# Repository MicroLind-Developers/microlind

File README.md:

# µLind
A 6809/6309 based micro computer with advanced memory and irq handling.

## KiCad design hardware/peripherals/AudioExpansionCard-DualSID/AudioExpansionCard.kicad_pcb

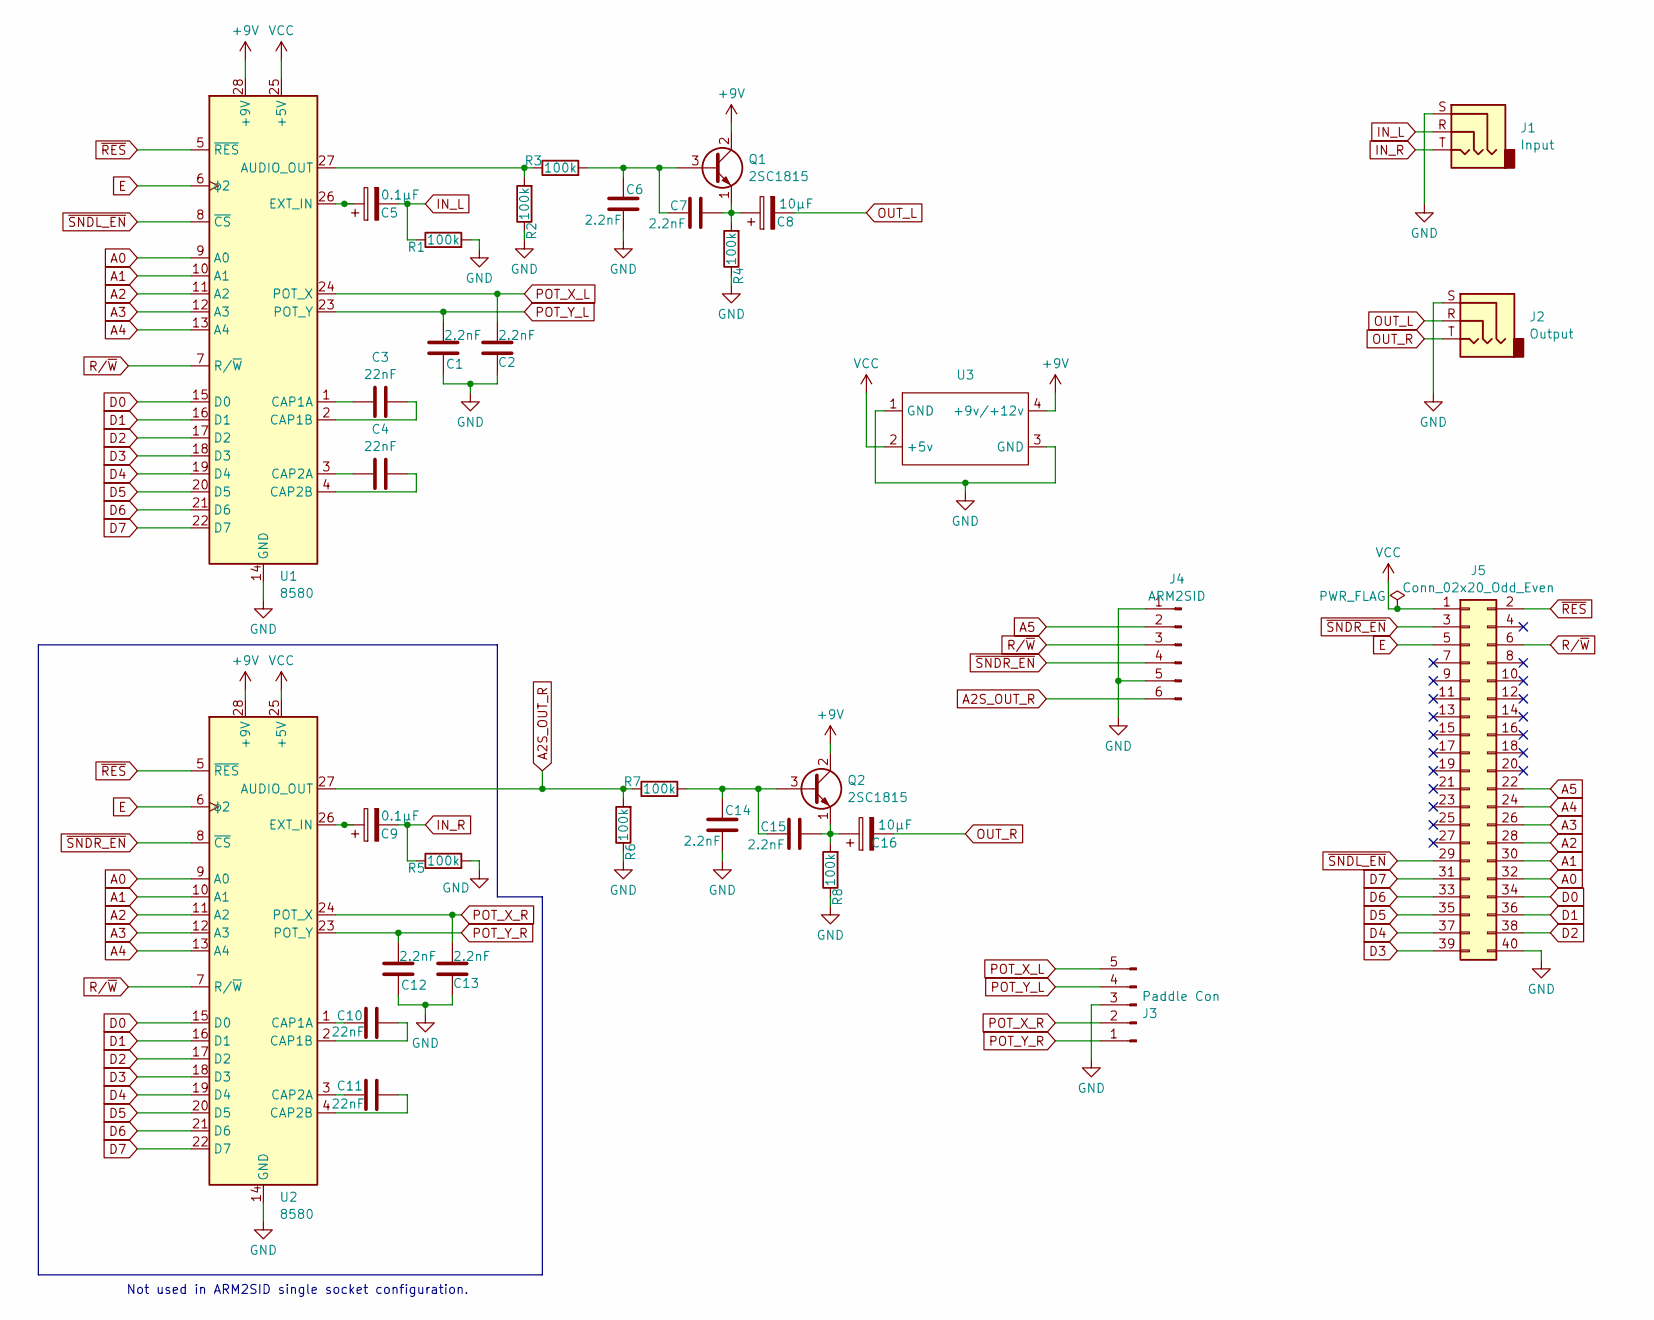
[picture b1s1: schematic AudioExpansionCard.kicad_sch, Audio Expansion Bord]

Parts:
C1, C2, C6, C7, C12, C13, C14, C15: 2.2nF; C_Disc_D3.0mm_W1.6mm_P2.50mm
C3, C4, C10, C11: 22nF; C_Disc_D3.0mm_W1.6mm_P2.50mm
C5, C9: 0.1µF; CP_Radial_D4.0mm_P1.50mm
C8, C16: 10µF; CP_Radial_D4.0mm_P1.50mm
J1: Input; Jack_3.5mm_CUI_SJ1-3533NG_Horizontal
J2: Output; Jack_3.5mm_CUI_SJ1-3533NG_Horizontal
J3: Paddle Con; PinHeader_1x05_P2.54mm_Horizontal
J4: ARM2SID; Molex_PicoBlade_53047-0610_1x06_P1.25mm_Vertical
J5: Conn_02x20_Odd_Even; AudioExpansionCard
Q1, Q2: 2SC1815; TO-92_Inline
R1, R2, R3, R4, R5, R6, R7, R8: 100k; R_Axial_DIN0207_L6.3mm_D2.5mm_P10.16mm_Horizontal
U1, U2: 8580; DIP-28_W15.24mm
U3: StepUpConverter

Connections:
+9V: Q1.2 (C), Q2.2 (C), U1.28 (+9V), U2.28 (+9V), U3.4 (+9v/+12v)
A0: J5.32, U1.9 (A0), U2.9 (A0)
A1: J5.30, U1.10 (A1), U2.10 (A1)
A2: J5.28, U1.11 (A2), U2.11 (A2)
A2S_OUT_R: J4.6, R6.2, R7.1, U2.27 (AUDIO_OUT)
A3: J5.26, U1.12 (A3), U2.12 (A3)
A4: J5.24, U1.13 (A4), U2.13 (A4)
A5: J4.2, J5.22
D0: J5.34, U1.15 (D0), U2.15 (D0)
D1: J5.36, U1.16 (D1), U2.16 (D1)
D2: J5.38, U1.17 (D2), U2.17 (D2)
D3: J5.39, U1.18 (D3), U2.18 (D3)
D4: J5.37, U1.19 (D4), U2.19 (D4)
D5: J5.35, U1.20 (D5), U2.20 (D5)
D6: J5.33, U1.21 (D6), U2.21 (D6)
D7: J5.31, U1.22 (D7), U2.22 (D7)
E: J5.5, U1.6 (ϕ2), U2.6 (ϕ2)
GND: C1.2, C2.2, C6.2, C12.2, C13.2, C14.2, J1.S, J2.S, J3.3, J4.1, J4.5, J5.40, R1.2, R2.1, R4.1, R5.2, R6.1, R8.1, U1.14 (GND), U2.14 (GND), U3.1 (GND), U3.3 (GND)
IN_L: C5.2, J1.R, R1.1
IN_R: C9.2, J1.T, R5.1
unnamed: C6.1, C7.1, Q1.3 (B), R3.2
unnamed: C7.2, C8.1, Q1.1 (E), R4.2
unnamed: C14.1, C15.1, Q2.3 (B), R7.2
unnamed: C15.2, C16.1, Q2.1 (E), R8.2
unnamed: R2.2, R3.1, U1.27 (AUDIO_OUT)
unnamed: C3.1, U1.1 (CAP1A)
unnamed: C3.2, U1.2 (CAP1B)
unnamed: C4.1, U1.3 (CAP2A)
unnamed: C4.2, U1.4 (CAP2B)
unnamed: C5.1, U1.26 (EXT_IN)
unnamed: C10.1, U2.1 (CAP1A)
unnamed: C10.2, U2.2 (CAP1B)
unnamed: C11.1, U2.3 (CAP2A)
unnamed: C11.2, U2.4 (CAP2B)
unnamed: C9.1, U2.26 (EXT_IN)
OUT_L: C8.2, J2.R
OUT_R: C16.2, J2.T
POT_X_L: C2.1, J3.5, U1.24 (POT_X)
POT_X_R: C13.1, J3.2, U2.24 (POT_X)
POT_Y_L: C1.1, J3.4, U1.23 (POT_Y)
POT_Y_R: C12.1, J3.1, U2.23 (POT_Y)
R/~W: J4.3, J5.6, U1.7 (R/~W), U2.7 (R/~W)
VCC: J5.1, U1.25 (+5V), U2.25 (+5V), U3.2 (+5v)
~RES: J5.2, U1.5 (~RES), U2.5 (~RES)
~SNDL_EN: J5.29, U1.8 (~CS)
~SNDR_EN: J4.4, J5.3, U2.8 (~CS)

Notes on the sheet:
Not used in ARM2SID single socket configuration.

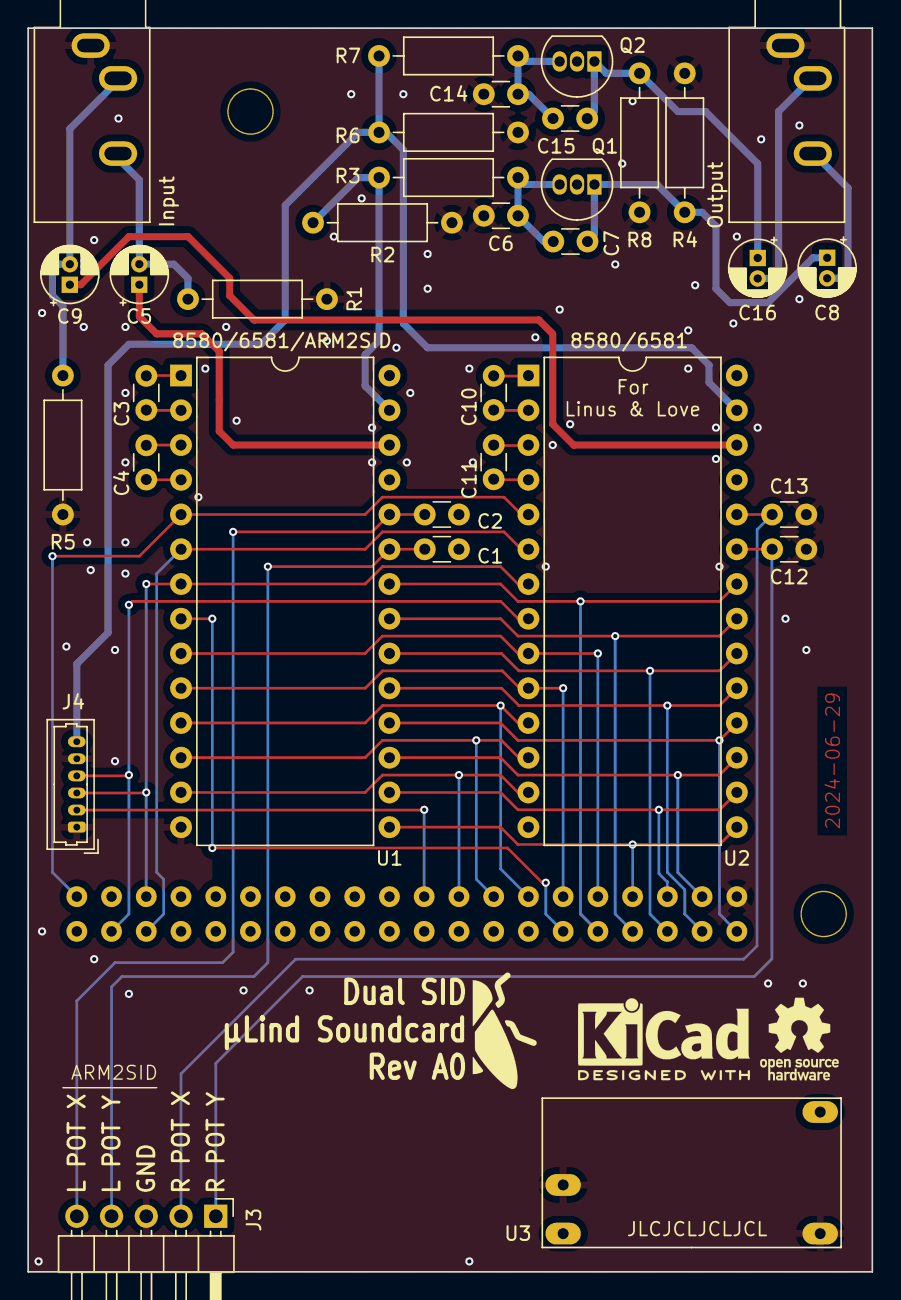
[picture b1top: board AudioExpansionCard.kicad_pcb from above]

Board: 4 copper layers, 61.7 x 90.9 mm, 34 parts (0 on the bottom side), 46 nets.

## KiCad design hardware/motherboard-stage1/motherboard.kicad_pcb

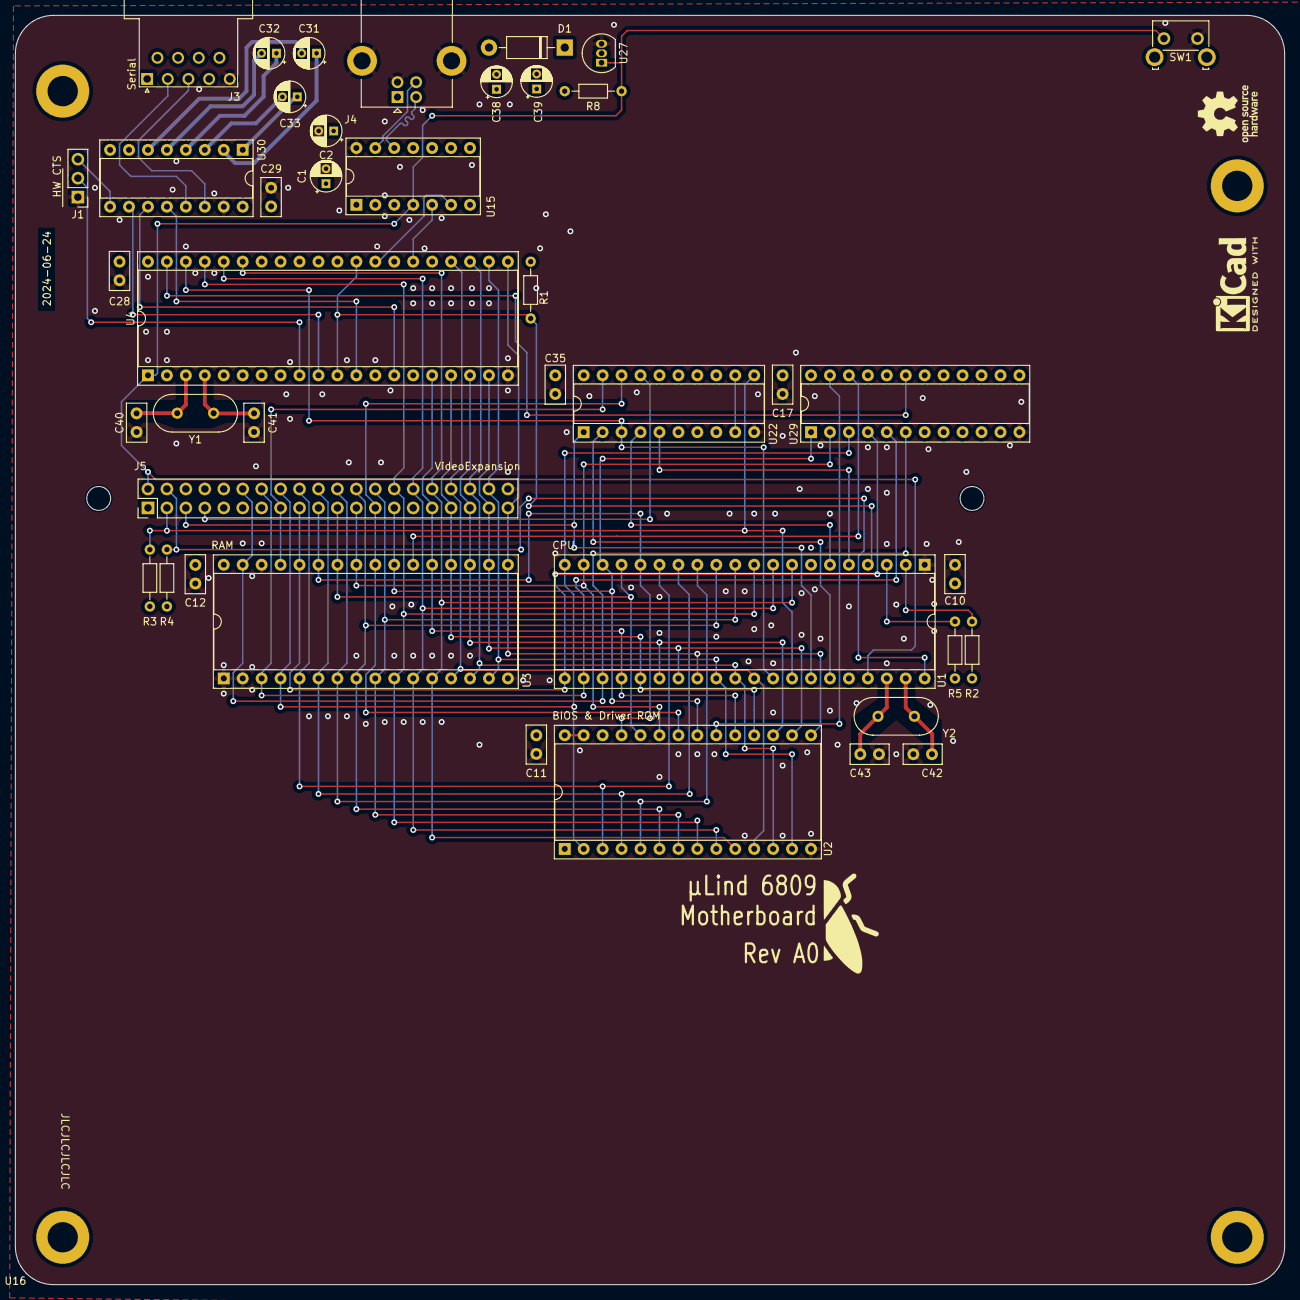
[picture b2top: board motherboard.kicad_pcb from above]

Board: 4 copper layers, 170.2 x 170.2 mm, 44 parts (0 on the bottom side), 69 nets.

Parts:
C1, C2, C31, C32, C33: 1u; CP_Radial_D4.0mm_P2.00mm
C10, C11, C12, C17, C28, C29, C35: C; C_Disc_D5.0mm_W2.5mm_P2.50mm
C38: 100µF; CP_Radial_D4.0mm_P2.00mm
C39: 10µF; CP_Radial_D4.0mm_P2.00mm
C40, C41: 43pF; C_Disc_D5.0mm_W2.5mm_P2.50mm
C42, C43: 24pF; C_Disc_D5.0mm_W2.5mm_P2.50mm
D1: 1N4007; D_DO-41_SOD81_P10.16mm_Horizontal
H6, H8: MountingHole; MountingHole_3.2mm_M3_ISO7380
J1: HW CTS; PinHeader_1x03_P2.54mm_Vertical
J3: Serial; DSUB-9_Female_Horizontal_P2.77x2.84mm_EdgePinOffset9.40mm
J4: Console; USB_B_Lumberg_2411_02_Horizontal
J5: VideoExpansion; PinHeader_2x20_P2.54mm_Vertical
R1, R2, R3, R4, R5, R8: 4k7; R_Axial_DIN0204_L3.6mm_D1.6mm_P7.62mm_Horizontal
SW1: Reset; SW_SPST_Omron_B3F-315x_Angled
U1: MC6809; DIP-40_W15.24mm_Socket
U2: 28C64; DIP-28_W15.24mm_Socket
U3: AS6C4008; DIP-32_W15.24mm_Socket
U4: DIP-40_W15.24mm_Socket
U15: MCP2221A; DIP-14_W7.62mm_Socket
U16: mITX
U22: GAL16V8; DIP-20_W7.62mm_Socket
U27: DS1813; TO-92_Inline
U29: GAL 22V10; DIP-24_W7.62mm_Socket
U30: MAX232; DIP-16_W7.62mm_Socket
Y1, Y2: Crystal; Crystal_HC49-U_Vertical

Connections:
/A0: J5.32, U1.8 (A0), U2.10 (A0), U3.12 (A0), U4.35 (RS0)
/A1: J5.30, U1.9 (A1), U2.9 (A1), U3.11 (A1), U4.36 (RS1)
/A2: J5.28, U1.10 (A2), U2.8 (A2), U3.10 (A2), U4.37 (RS2)
/A3: J5.26, U1.11 (A3), U2.7 (A3), U3.9 (A3)
/A4: J5.24, U1.12 (A4), U2.6 (A4), U3.8 (A4)
/A5: J5.22, U1.13 (A5), U2.5 (A5), U3.7 (A5)
/A6: J5.20, U1.14 (A6), U2.4 (A6), U3.6 (A6)
/A7: J5.18, U1.15 (A7), U2.3 (A7), U3.5 (A7)
/A8: J5.19, U1.16 (A8), U2.25 (A8), U3.27 (A8)
/A9: J5.21, U1.17 (A9), U2.24 (A9), U3.26 (A9)
/A10: J5.27, U1.18 (A10), U2.21 (A10), U3.23 (A10), U29.1 (I1/CLK)
/A11: J5.23, U1.19 (A11), U2.23 (A11), U3.25 (A11), U29.2 (I2)
/A12: J5.16, U1.20 (A12), U2.2 (A12), U3.4 (A12), U29.3 (I3)
/A13: J5.17, U1.21 (A13), U3.28 (A13), U29.4 (I4)
/A14: J5.14, U1.22 (A14), U3.3 (A14), U29.5 (I5)
/A15: J5.12, U1.23 (A15), U3.31 (A15), U29.6 (I6)
/Address-Logic/BA: U1.6 (BA), U22.4 (I4)
/Address-Logic/BS: U1.5 (BS), U22.5 (I5)
/Address-Logic/Q: U1.35 (Q), U22.2 (I2)
/Address-Logic/R/~W: U1.32 (R/~W), U4.38 (R~W), U22.3 (I3)
/Address-Logic/~RAM_EN: U3.22 (CE#), U29.22 (IO2)
/Address-Logic/~ROM_EN: U2.20 (~CE), U29.23 (IO1)
/Address-Logic/~SER_EN: U4.39 (~CS), U29.19 (IO5)
/CPU_MEM/~FIRQ: R1.1, U1.4 (~FIRQ), U4.11 (~IRQ2), U4.29 (~IRQ1)
/CPU_MEM/~HALT: J5.4, R4.1, U1.40 (~HALT)
/CPU_MEM/~IRQ: R5.1, U1.3 (~IRQ)
/CPU_MEM/~NMI: R2.1, U1.2 (~NMI)
/D0: J5.34, U1.31 (D0), U2.11 (D0), U3.13 (DQ0), U4.24 (D0)
/D1: J5.36, U1.30 (D1), U2.12 (D1), U3.14 (DQ1), U4.23 (D1)
/D2: J5.38, U1.29 (D2), U2.13 (D2), U3.15 (DQ2), U4.22 (D2)
/D3: J5.39, U1.28 (D3), U2.15 (D3), U3.17 (DQ3), U4.21 (D3)
/D4: J5.37, U1.27 (D4), U2.16 (D4), U3.18 (DQ4), U4.19 (D4)
/D5: J5.35, U1.26 (D5), U2.17 (D5), U3.19 (DQ5), U4.18 (D5)
/D6: J5.33, U1.25 (D6), U2.18 (D6), U3.20 (DQ6), U4.17 (D6)
/D7: J5.31, U1.24 (D7), U2.19 (D7), U3.21 (DQ7), U4.16 (D7)
/Expansion Ports/BAVAIL: J5.7, U22.17 (I03)
/Expansion Ports/E: J5.5, U1.34 (E), U22.1 (I1/CLK)
/Expansion Ports/~BREQ: J5.3, R3.1, U1.33 (~DMA/BREQ), U22.11 (I10/~OE)
/Expansion Ports/~RD: J5.25, U2.22 (~OE), U3.24 (OE#), U22.18 (IO2)
/Expansion Ports/~RST: J5.2, R8.2, SW1.1, U1.37 (~RESET), U4.1 (~RST), U15.4 (~RST), U27.1 (~RST)
/Expansion Ports/~WR: J5.15, U3.29 (WE#), U22.19 (IO1)
/Serial-Parallel/D+: J4.3 (D+), U15.13 (D+)
/Serial-Parallel/D-: J4.2 (D-), U15.12 (D-)
GND: C1.2, C2.2, C10.2, C11.2, C12.2, C17.2, C28.2, C29.2, C35.2, C40.2, C41.2, C42.2, C43.2, J1.1, J3.5, J4.4 (GND), J4.5 (Shield), J5.40, SW1.2, U1.1 (VSS), U2.14 (GND), U3.1 (A18), U3.2 (A16), U3.16 (VSS), U3.30 (A17), U4.20 (Vss), U15.14 (VSS), U22.10 (GND), U27.3 (GND), U29.12 (GND), U30.15 (GND)
unnamed: J1.2, U4.9 (~CTS2)
unnamed: J1.3, U30.9 (R2OUT)
unnamed: C43.1, U1.38 (EXTAL), Y2.1
unnamed: C42.1, U1.39 (XTAL), Y2.2
unnamed: C40.1, U4.3 (X1), Y1.2
unnamed: C41.1, U4.4 (X2), Y1.1
unnamed: U4.26 (TxD1), U15.5 (URx)
unnamed: U4.28 (RxD1), U15.6 (UTx)
unnamed: C2.1, U15.11 (VUSB)
unnamed: C33.1, U30.1 (C1+)
unnamed: C33.2, U30.3 (C1-)
unnamed: C32.1, U30.4 (C2+)
unnamed: C32.2, U30.5 (C2-)
unnamed: J3.2, U30.13 (R1IN)
unnamed: U4.12 (RxD2), U30.12 (R1OUT)
unnamed: J3.8, U30.8 (R2IN)
unnamed: U4.14 (TxD2), U30.11 (T1IN)
unnamed: J3.3, U30.14 (T1OUT)
unnamed: U4.10 (~RTS2), U30.10 (T2IN)
unnamed: J3.7, U30.7 (T2OUT)
unnamed: C31.1, U30.2 (VS+)
unnamed: C31.2, U30.6 (VS-)
VBUS: C1.1, C38.1, C39.1, D1.2 (A), J4.1 (VBUS), U15.1 (VDD)
VCC: C10.1, C11.1, C12.1, C17.1, C28.1, C29.1, C35.1, C38.2, C39.2, D1.1 (K), J5.1, R1.2, R2.2, R3.2, R4.2, R5.2, R8.1, U1.7 (VCC), U2.27 (~WE), U2.28 (VCC), U3.32 (VCC), U4.40 (VCC), U22.20 (VCC), U27.2 (VCC), U29.24 (VCC), U30.16 (VCC)
~RD': U22.9 (I9), U22.12 (IO8)

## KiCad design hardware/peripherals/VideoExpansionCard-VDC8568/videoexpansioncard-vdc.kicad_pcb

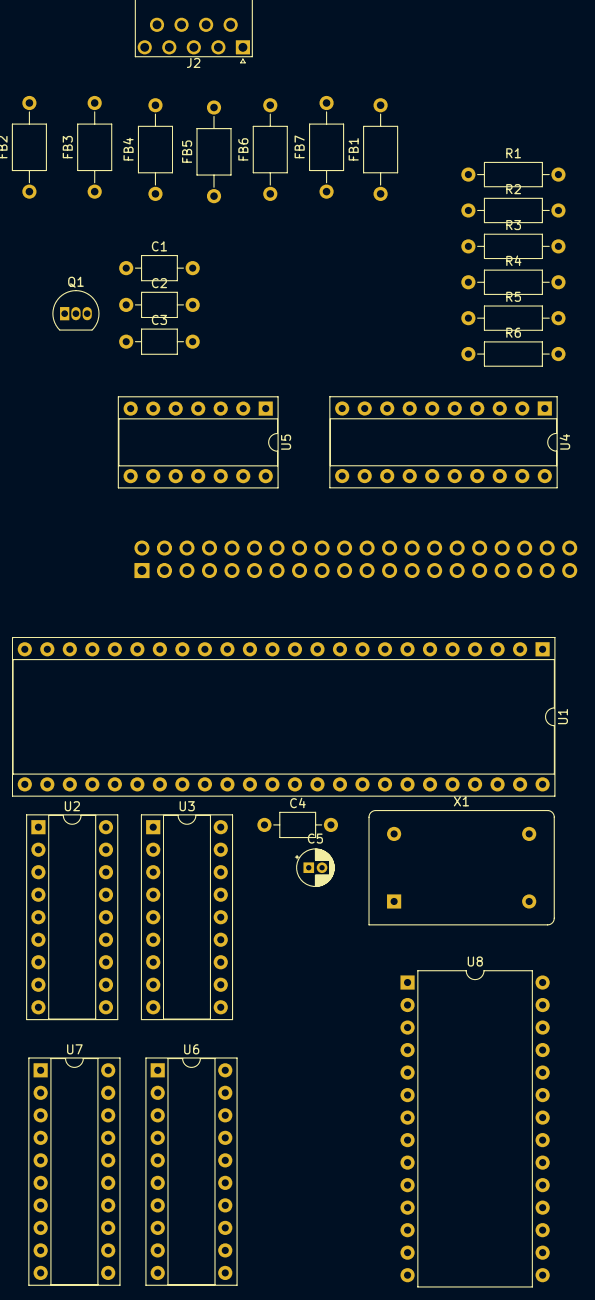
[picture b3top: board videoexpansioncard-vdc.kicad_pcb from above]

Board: 2 copper layers, 30 parts (1 on the bottom side), 69 nets, no tracks yet.

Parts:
C1, C4: 100nF; C_Axial_L3.8mm_D2.6mm_P7.50mm_Horizontal
C2, C3: 220nF; C_Axial_L3.8mm_D2.6mm_P7.50mm_Horizontal
C5: 10µF; CP_Radial_D4.0mm_P1.50mm
FB1, FB2, FB3, FB4, FB5, FB6, FB7: FerriteBead_Small; L_Axial_L5.0mm_D3.6mm_P10.00mm_Horizontal_Murata_BL01RN1A2A2
J1: VEP; PinSocket_2x20_P2.54mm_Vertical
J2: DE9_Plug; DSUB-9_Male_Horizontal_P2.77x2.54mm_EdgePinOffset9.40mm
Q1: 2SC1815; TO-92_Inline
R1, R2: 120; R_Axial_DIN0207_L6.3mm_D2.5mm_P10.16mm_Horizontal
R3: 100; R_Axial_DIN0207_L6.3mm_D2.5mm_P10.16mm_Horizontal
R4: 330; R_Axial_DIN0207_L6.3mm_D2.5mm_P10.16mm_Horizontal
R5: 47; R_Axial_DIN0207_L6.3mm_D2.5mm_P10.16mm_Horizontal
R6: 82; R_Axial_DIN0207_L6.3mm_D2.5mm_P10.16mm_Horizontal
U1: 8568; DIP-48_W15.24mm_Socket
U2, U3: DIP-18_W7.62mm_Socket
U4: 74HCT244; DIP-20_W7.62mm_Socket
U5: 74LS07; DIP-14_W7.62mm_Socket
U6: 74HCT273; DIP-20_W7.62mm_Socket
U7: GAL16V8; DIP-20_W7.62mm_Socket
U8: 27C64; DIP-28_W15.24mm
X1: ACO-16MHz; Oscillator_DIP-14

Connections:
/DRAM.DA0: U1.26 (DA0), U2.14 (A0), U3.14 (A0)
/DRAM.DA1: U1.27 (DA1), U2.13 (A1), U3.13 (A1)
/DRAM.DA2: U1.28 (DA2), U2.12 (A2), U3.12 (A2)
/DRAM.DA3: U1.29 (DA3), U2.11 (A3), U3.11 (A3)
/DRAM.DA4: U1.30 (DA4), U2.8 (A4), U3.8 (A4)
/DRAM.DA5: U1.31 (DA5), U2.7 (A5), U3.7 (A5)
/DRAM.DA6: U1.32 (DA6), U2.6 (A6), U3.6 (A6)
/DRAM.DA7: U1.33 (DA7), U2.10 (A7), U3.10 (A7)
/DRAM.DD0: U1.34 (DD0), U2.2 (D0)
/DRAM.DD1: U1.35 (DD1), U2.3 (D1)
/DRAM.DD2: U1.36 (DD2), U2.15 (D2)
/DRAM.DD3: U1.38 (DD3), U2.17 (D3)
/DRAM.DD4: U1.39 (DD4), U3.2 (D0)
/DRAM.DD5: U1.40 (DD5), U3.3 (D1)
/DRAM.DD6: U1.41 (DD6), U3.15 (D2)
/DRAM.DD7: U1.42 (DD7), U3.17 (D3)
/DRAM.~CAS: U1.1 (~CAS), U2.16 (~CAS), U3.16 (~CAS)
/DRAM.~RAS: U1.48 (~RAS), U2.5 (~RAS), U3.5 (~RAS)
/DRAM.~W: U1.21 (DR/W), U2.4 (~W), U3.4 (~W)
A0: J1.32, U1.7 (~RS)
D0: J1.34, U1.18 (D0), U8.11 (D0)
D1: J1.36, U1.17 (D1), U8.12 (D1)
D2: J1.38, U1.16 (D2), U8.13 (D2)
D3: J1.39, U1.15 (D3)
D4: J1.37, U1.14 (D4)
D5: J1.35, U1.13 (D5)
D6: J1.33, U1.11 (D6)
D7: J1.31, U1.10 (D7)
GND: C1.2, C2.2, C3.2, C4.2, C5.2, J1.40, J2.1, J2.2, R1.2, R6.2, U1.12 (GND), U1.23 (INIT), U1.24 (TEST), U2.1 (~G), U2.18 (GND), U3.1 (~G), U3.18 (GND), U4.1 (1OE), U4.10 (GND), U4.11 (2A3), U4.13 (2A2), U4.19 (2OE), U5.7 (GND), U5.9, U5.11, U5.13, X1.7 (GND)
unnamed: FB1.2, J2.5
unnamed: FB2.2, J2.9
unnamed: FB3.2, J2.4
unnamed: FB4.2, J2.8
unnamed: FB5.2, J2.3
unnamed: FB6.2, J2.7
unnamed: FB7.2, J2.6
unnamed: Q1.3 (B), R3.2, R4.1, U5.4
unnamed: Q1.2 (C), R5.2
unnamed: FB6.1, Q1.1 (E), R6.1
unnamed: R1.1, R2.1, U5.6
unnamed: R2.2, R3.1, U5.2
unnamed: U1.44 (B), U4.6 (1A2)
unnamed: U1.19 (CSYNC), U5.3
unnamed: U1.47 (CV), U5.1
unnamed: U1.45 (G), U4.4 (1A1)
unnamed: U1.4 (HSYNC), U4.15 (2A1)
unnamed: U1.43 (I), U4.8 (1A3), U5.5
unnamed: U1.46 (R), U4.2 (1A0)
unnamed: U1.20 (VSYNC), U4.17 (2A0)
unnamed: U1.3 (~DCLK), X1.8 (OUT)
unnamed: FB5.1, U4.18 (1Y0)
unnamed: FB3.1, U4.16 (1Y1)
unnamed: FB1.1, U4.14 (1Y2)
unnamed: FB7.1, U4.12 (1Y3)
unnamed: FB2.1, U4.3 (2Y0)
unnamed: FB4.1, U4.5 (2Y1)
unnamed: U6.2 (Q0), U8.5 (A5)
unnamed: U6.5 (Q1), U8.4 (A6)
unnamed: U6.6 (Q2), U8.3 (A7)
unnamed: U6.9 (Q3), U8.25 (A8)
unnamed: U6.12 (Q4), U8.24 (A9)
unnamed: U6.15 (Q5), U8.21 (A10)
unnamed: U6.16 (Q6), U8.23 (A11)
unnamed: U6.19 (Q7), U8.2 (A12)
R/~W: J1.6, U1.8 (R/W)
VCC: C1.1, C2.1, C3.1, C4.1, C5.1, J1.1, R4.2, R5.1, U1.37 (VCC), U2.9 (Vcc), U3.9 (Vcc), U4.20 (VCC), U5.14 (VCC), X1.14 (Vcc)
~RST: J1.2, U1.22 (~RES)
~VDC_EN: J1.29, U1.6 (~CS)
~VDC_IRQ: J1.4, U1.9 (~INT)

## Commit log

2024-01-15 initial structure
2024-06-24 Last updates of motherboard
2024-07-02 A lot of updates
2024-07-31 Splitting the repo into separate parts for firmware, software and hardware. This repo will hold them together and maintain releases and documents
2024-10-16 Added microlind-sw subrepo.
2024-10-16 Updated subrepos
2024-10-16 Added sw
2024-10-16 Fixed paths
2024-10-16 Bump subrepos
2024-10-28 Updates to hardware
2024-10-30 Updates to a lot of stuf
2024-10-30 Update fw
2024-10-30 hmmm...
2024-10-30 Readded submodules due to renaming
2024-10-31 Updated gitmodules to the new repo
2024-11-15 Updates to hw and builder
2025-04-01 Added info and bumped repos
2025-04-23 Bumping all the things and addind stage2 release
2025-04-25 Stage 2 bump!
2025-04-25 Bump of all the things
2025-08-05 Updated hw/sw and added some proto test files
2025-08-05 Added stage 3 schematics
2025-08-12 General bump, updates to all subrepos
